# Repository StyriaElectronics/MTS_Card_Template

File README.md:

# 🧩 MTS (Modular Test System) – Card Template

The **Modular Test System – Card Template** provides a base design for plug-in boards that slide into a standard **3U 42TE rack**.  
These boards interface with a central **backplane**, enabling power distribution and inter-module communication.  
Perfect for rapid development of sensor, signal, communication, or analog cards — with a clean KiCad layout ready to extend.

---

---

## 📦 Project Contents

- `.kicad_pro` – Project file
- `.kicad_sch` – Schematic
- `.kicad_pcb` – PCB layout
- `*-backups/*.zip` – Gerber backup ZIPs for production
- `.gitignore`, `LICENSE`, `README.md`

---

## 🛠 Requirements

- [KiCad 8.x](https://www.kicad.org/)
- Optional: [Gerber Viewer](https://gerbv.geda-project.org/) or JLCPCB/PCBWay web viewer

---

## 🚀 Open the Project

```bash
# Clone the repository
git clone https://github.com/StyriaElectronics/MTS_Card_Template.git

# Open the project in KiCad
open MTS_Card_Template.kicad_pro
```

---

## 📘 MTS System – Technical Specification

- 📄 [🇩🇪 Deutsch – MTS_Specification.md](specs/MTS_Specification.md)  
- 📄 [🇬🇧 English – MTS_Specification_EN.md](specs/MTS_Specification_EN.md)

---

## 🧪 Export Gerber Files

To export new Gerber files from KiCad:

1. Open the `.kicad_pcb` file in KiCad
2. Go to File > Plot > Gerber
3. Optionally, ZIP the result:
   ```bash
   zip -r Gerber_Export.zip <folder>
   ```

---

## 📃 License

This project is licensed under the  
**[Creative Commons Attribution 4.0 International (CC BY 4.0)](https://creativecommons.org/licenses/by/4.0/)** license.

> You may use, modify, and share the project – **as long as you give proper credit to the author**.

Author: **Styria Electronics András Nagy**  
Website: [styria-electronics](https://styria-electronics.at)

---
## ⚠️ Disclaimer
This project is provided "as is" without warranty of any kind, either expressed or implied.  
In no event shall the author(s) be liable for any claim, damages, or other liability arising from, out of, or in connection with the use or other dealings in this project.

## 🤝 Contributing

Pull requests, issues, and forks are always welcome!

---

## ⭐️ If You Like It...

... give this project a star ⭐️ on GitHub!

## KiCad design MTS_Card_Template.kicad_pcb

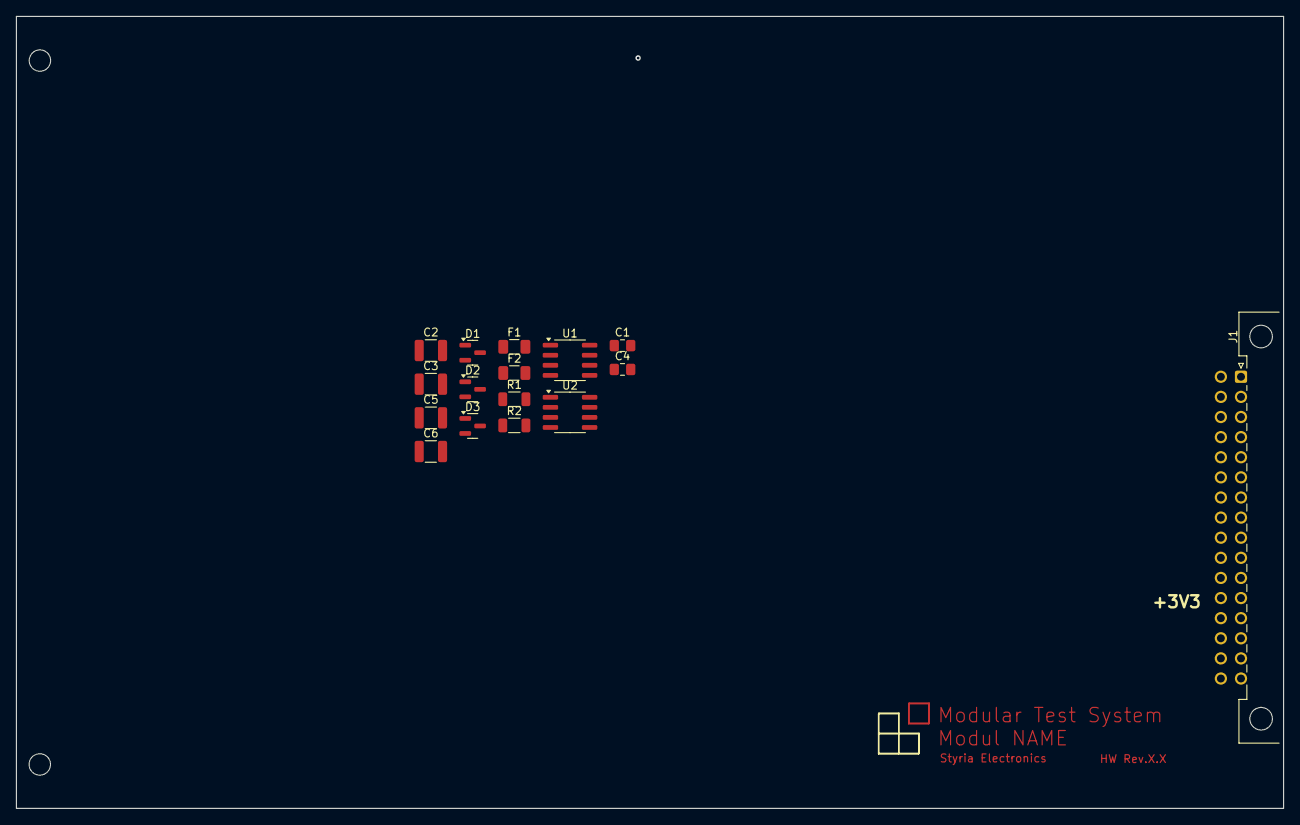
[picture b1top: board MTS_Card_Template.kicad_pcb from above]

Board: 6 copper layers, 160.0 x 100.0 mm, 19 parts (1 on the bottom side), 16 nets.

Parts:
C1, C4: 100nF; C_0805_2012Metric_Pad1.18x1.45mm_HandSolder
C2, C3, C5, C6: 47µF; C_1210_3225Metric
D1: PESD3V3L2BT; SOT-23
D2, D3: PESD2CANFD24V-T; SOT-23
F1, F2: Fuse; Fuse_1206_3216Metric
J1: DIN41612_02x16_ZB; DIN41612_B2_2x16_Male_Horizontal_THT
MH1, MH3: MountingHole_2.7mm_M2.5_DIN965
QR Code: LOGO
R1, R2: 0.20Ω; R_1206_3216Metric
U1, U2: INA219AxD; SOIC-8_3.9x4.9mm_P1.27mm

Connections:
+3V3: R1.2, R2.2, U1.5 (VS), U1.7 (IN-), U2.1 (A1), U2.5 (VS), U2.7 (IN-)
+3V3Ext: C1.1, C2.1, C3.1, C4.1, C5.1, C6.1, F1.2, F2.2, J1.a13 (Pin_z13), J1.a14 (Pin_z14)
+5VExt: J1.a15 (Pin_z15), J1.a16 (Pin_z16)
+12V: J1.a11 (Pin_z11), J1.a12 (Pin_z12)
-12V: J1.b11, J1.b12
/Conn/CAN_H: D3.2 (K), J1.b1
/Conn/CAN_L: D3.1 (K), J1.b2
/Conn/I2C_BUS_CLK: D2.1 (K), J1.b4
/Conn/I2C_BUS_SDA: D2.2 (K), J1.b3
/Conn/SYNC_CPU: D1.1 (K), J1.a2 (Pin_z2)
/Conn/Triger: D1.2 (K), J1.a1 (Pin_z1)
GND: C1.2, C2.2, C3.2, C4.2, C5.2, C6.2, D1.3 (A), D2.3 (A), D3.3 (A), J1.b13, J1.b14, J1.b15, J1.b16, U1.1 (A1), U1.2 (A0), U1.6 (GND), U2.2 (A0), U2.6 (GND)
I2C1_SCL: U1.4 (SCL), U2.4 (SCL)
I2C1_SDA: U1.3 (SDA), U2.3 (SDA)
unnamed: F1.1, R1.1, U1.8 (IN+)
unnamed: F2.1, R2.1, U2.8 (IN+)

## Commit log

2025-04-07 Backups aus .gitignore entfernt
2025-04-07 Clean up: .gitignore hinzugefügt
2025-04-07 Lokale Änderungen vor dem Pull gesichert
2025-04-07 Remove backups from Git tracking
2025-04-07 ADD Badges README.md
2025-04-07 ADD LICENSE File
2025-04-07 Edit Connector
2025-04-07 ADD Meta for Template
2025-04-07 ADD index.html
2025-04-07 Add MTS Specification
2025-04-08 Bug Fix
2025-05-21 Update Connector

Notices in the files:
README.md:
License: CC BY 4.0
